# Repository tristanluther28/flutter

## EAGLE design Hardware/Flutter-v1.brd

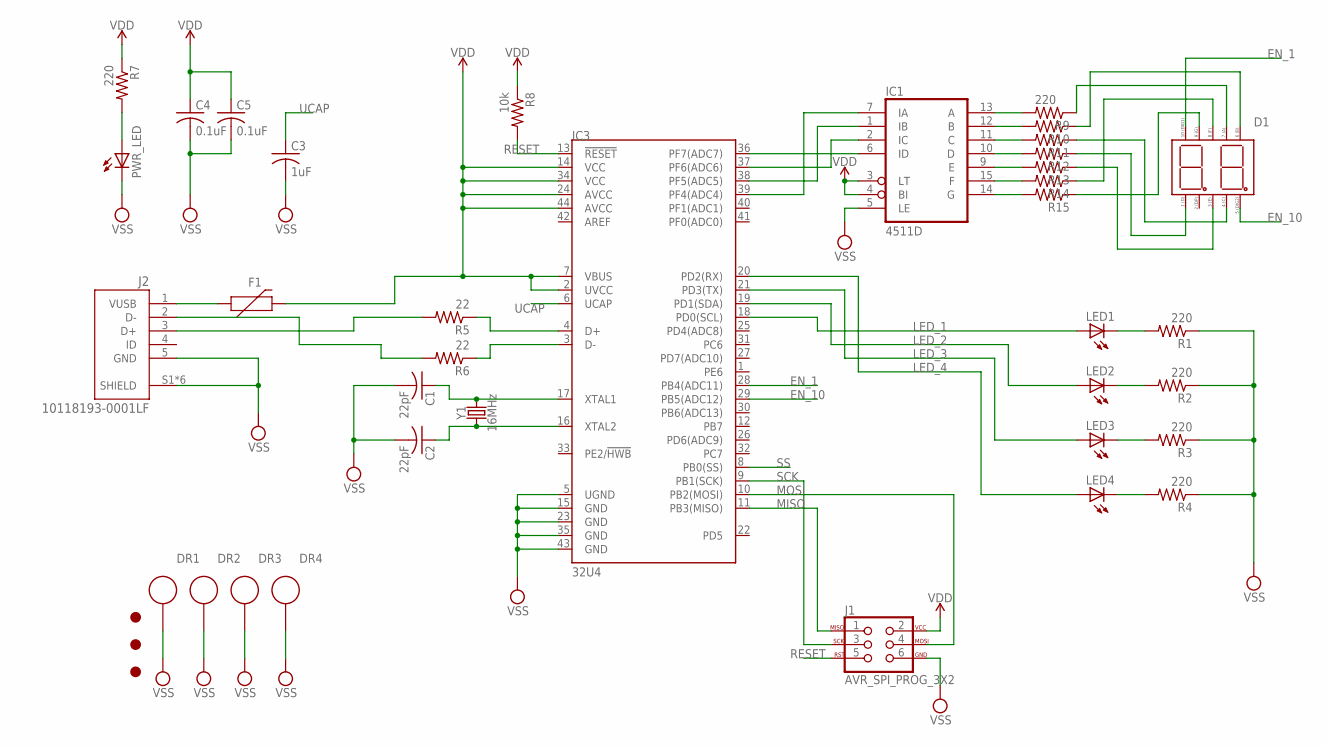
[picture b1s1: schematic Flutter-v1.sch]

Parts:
C1, C2: 22pF; C0805
C3: 1uF; C0805
C4, C5: 0.1uF; C0805
D1: 4201AS
DR1, DR2, DR3, DR4: 3MM_DRILL_GND
F1: 6V/0.5A; 1206
IC1: 4511D; SO16
IC3: 32U4; TQFP44
J1: AVR_SPI_PROG_3X2; 2X3-NS
J2: 10118193-0001LF; FCI_10118193-0001LF
LED1, LED2, LED3, LED4: LED5MM
PWR_LED: LEDCHIPLED_0603; CHIPLED_0603
R1, R2, R3, R4, R7, R9, R10, R11, R12, R13, R14, R15: 220; M0805
R5, R6: 22; M0805
R8: 10k; M0805
U$4, U$5, U$6: FIDUCIAL_MARKER
Y1: 16MHz; CRYSTAL-SMD-5X3.2-4PAD

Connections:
EN_1: D1.10, IC3.28 (PB4(ADC11))
EN_10: D1.5 (5(DIG_2)), IC3.29 (PB5(ADC12))
LED_1: IC3.18 (PD0(SCL)), LED1.A
LED_2: IC3.19 (PD1(SDA)), LED2.A
LED_3: IC3.21 (PD3(TX)), LED3.A
LED_4: IC3.20 (PD2(RX)), LED4.A
MISO: IC3.11 (PB3(MISO)), J1.1
MOSI: IC3.10 (PB2(MOSI)), J1.4
unnamed: IC3.4 (D+), R5.1
unnamed: IC3.3 (D-), R6.1
unnamed: J2.3 (D+), R5.2
unnamed: J2.2 (D-), R6.2
unnamed: PWR_LED.A, R7.2
unnamed: C1.1, IC3.17 (XTAL1), Y1.3 (2)
unnamed: C2.1, IC3.16 (XTAL2), Y1.1
unnamed: IC1.13 (A), R9.2
unnamed: LED1.K (C), R1.2
unnamed: LED2.K (C), R2.2
unnamed: LED3.K (C), R3.2
unnamed: LED4.K (C), R4.2
unnamed: IC1.12 (B), R10.2
unnamed: IC1.11 (C), R11.2
unnamed: IC1.10 (D), R12.2
unnamed: IC1.9 (E), R13.2
unnamed: IC1.15 (F), R14.2
unnamed: IC1.14 (G), R15.2
unnamed: F1.1, J2.1 (VUSB)
unnamed: D1.7 (7(A)), R9.1
unnamed: D1.6 (6(B)), R10.1
unnamed: D1.4 (4(C)), R11.1
unnamed: IC1.7 (IA), IC3.39 (PF4(ADC4))
unnamed: IC1.1 (IB), IC3.38 (PF5(ADC5))
unnamed: IC1.2 (IC), IC3.37 (PF6(ADC6))
unnamed: IC1.6 (ID), IC3.36 (PF7(ADC7))
unnamed: D1.1 (1(D)), R12.1
unnamed: D1.3 (3(E)), R13.1
unnamed: D1.8 (8(F)), R14.1
unnamed: D1.9 (9(G)), R15.1
RESET: IC3.13 (!RESET), J1.5, R8.2
SCK: IC3.9 (PB1(SCK)), J1.3
SS: IC3.8 (PB0(SS))
UCAP: C3.1, IC3.6 (UCAP)
VDD: C4.1, C5.1, F1.2, IC1.3 (LT), IC1.4 (BI), IC1.16 (VDD), IC3.2 (UVCC), IC3.7 (VBUS), IC3.14 (VCC), IC3.24 (AVCC), IC3.34 (VCC), IC3.44 (AVCC), J1.2, R7.1, R8.1
VSS: C1.2, C2.2, C3.2, C4.2, C5.2, DR1.DR, DR2.DR, DR3.DR, DR4.DR, IC1.5 (LE), IC1.8 (VSS), IC3.5 (UGND), IC3.15 (GND), IC3.23 (GND), IC3.35 (GND), IC3.43 (GND), J1.6, J2.5 (GND), J2.S1 (SHIELD), J2.S2 (SHIELD), J2.S3 (SHIELD), J2.S4 (SHIELD), J2.S5 (SHIELD), J2.S6 (SHIELD), PWR_LED.C, R1.1, R2.1, R3.1, R4.1

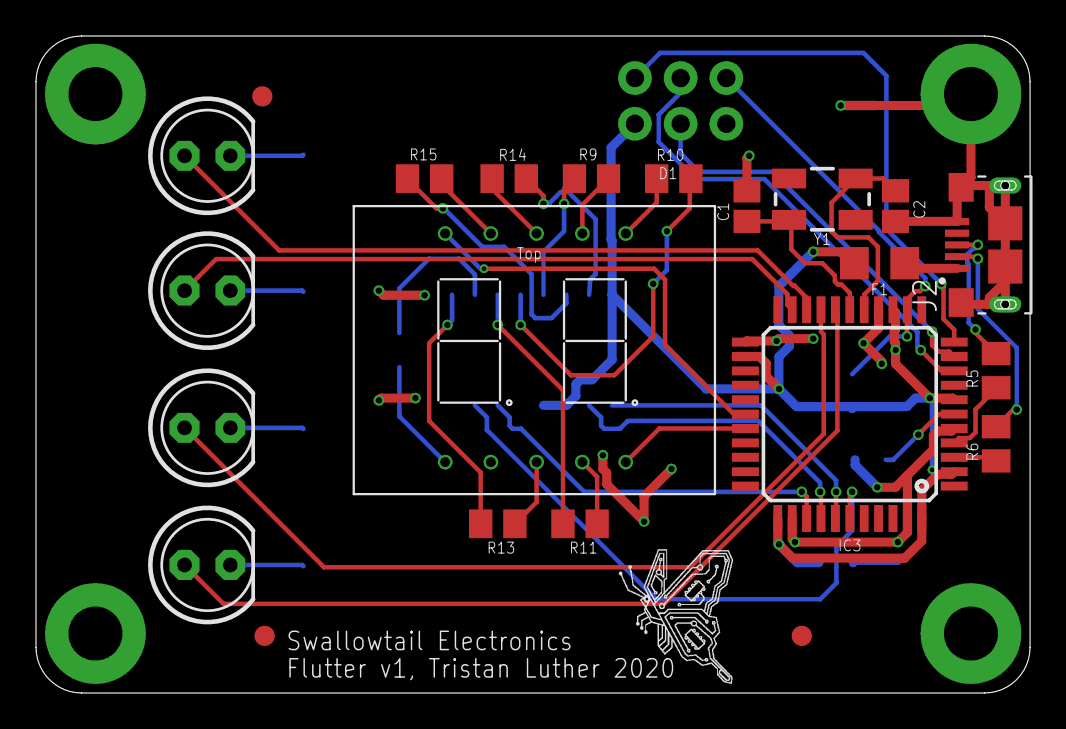
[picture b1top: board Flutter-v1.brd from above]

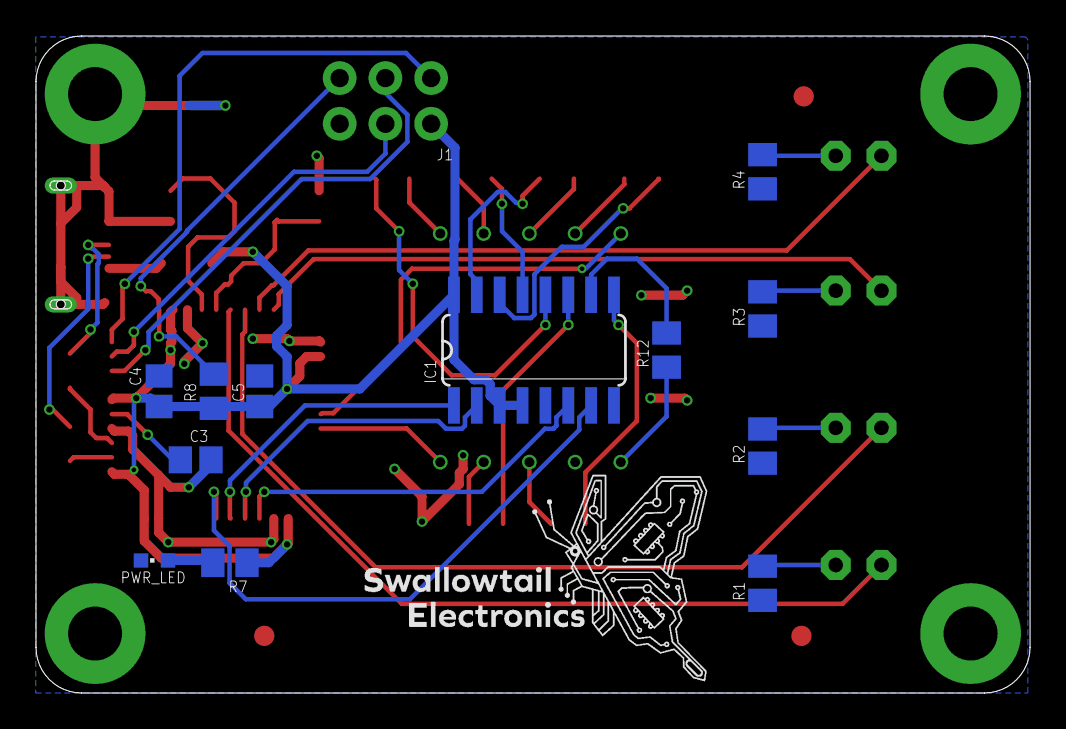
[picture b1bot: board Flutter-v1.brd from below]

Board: 2 copper layers, 55.2 x 36.5 mm, 41 parts (14 on the bottom side), 43 nets.

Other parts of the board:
U$2: SWALLOWTAIL_LOGO
U$3: SMALL_SWALLOWTAIL_NO_TEXT

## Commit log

2021-04-27 Added files & layout
    Real initial commit

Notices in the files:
parts and their libraries:
SparkFun-IC-Microcontroller: Licensing: Creative Commons ShareAlike 4.0 International - https://creativecommons.org/licenses/by-sa/4.0
